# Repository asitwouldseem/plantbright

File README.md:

# plantbright
Just another A6211 based LED driver project for illuminating house plants.

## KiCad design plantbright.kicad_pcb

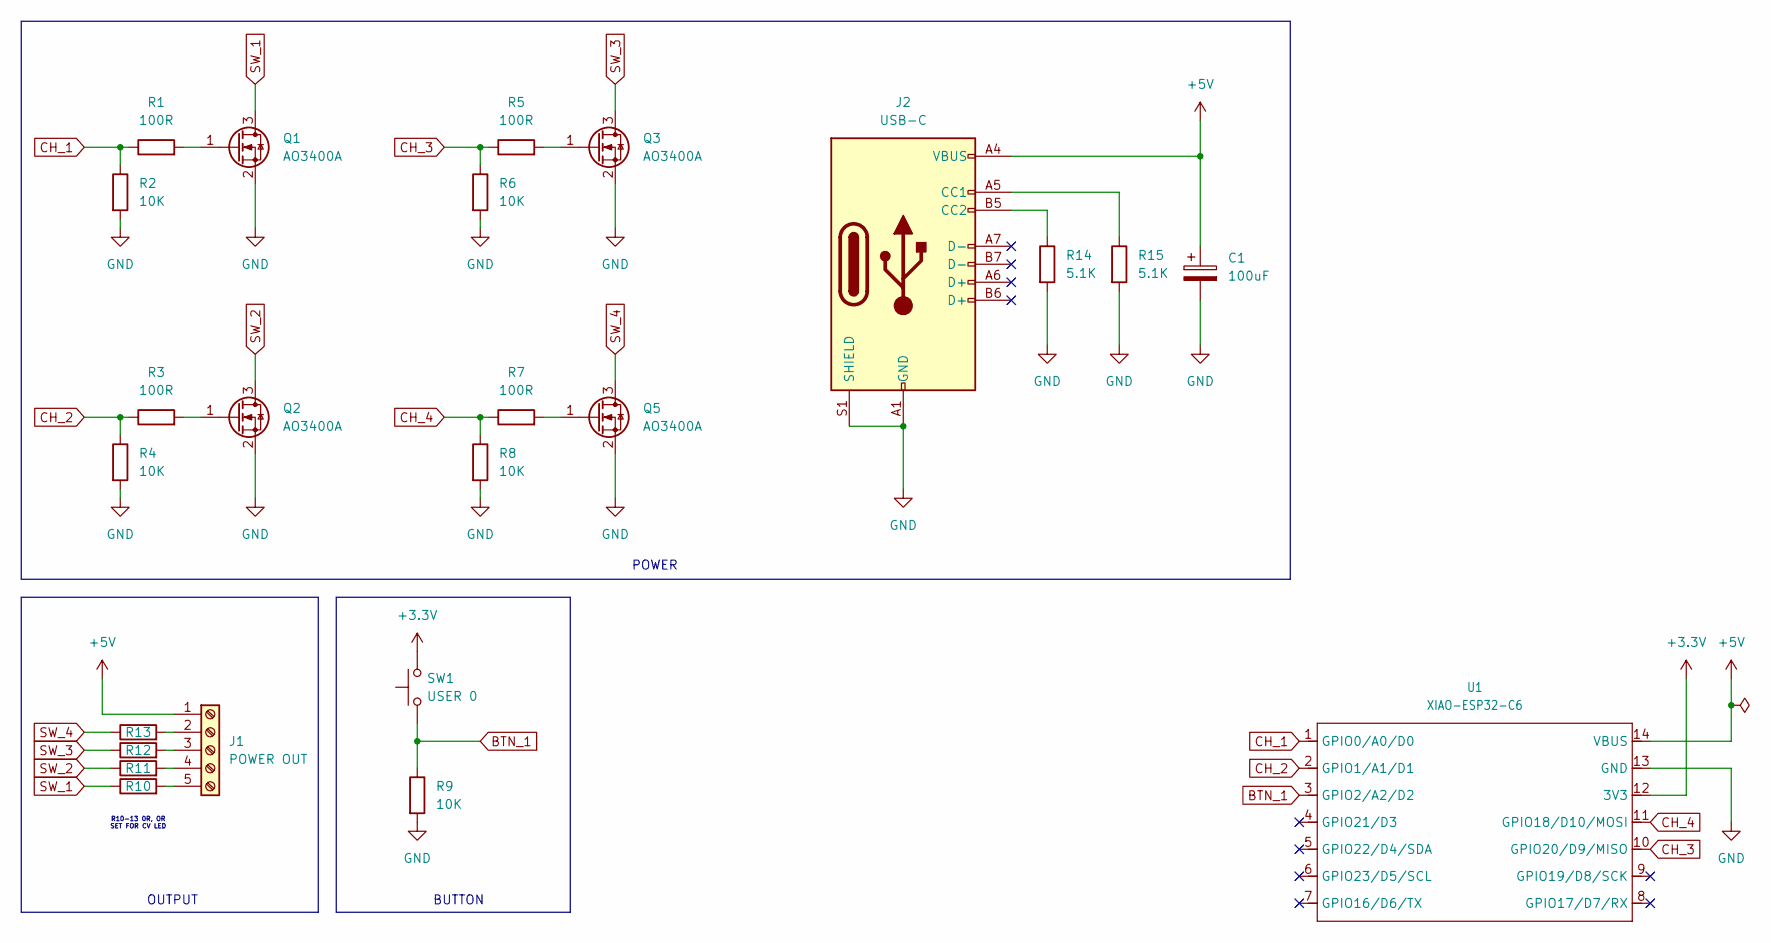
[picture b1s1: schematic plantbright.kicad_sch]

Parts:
C1: 100uF; C_1206_3216Metric_Pad1.33x1.80mm_HandSolder
J1: POWER OUT; TerminalBlock_Phoenix_MPT-0,5-5-2.54_1x05_P2.54mm_Horizontal
J2: USB-C; USB_C_Receptacle_HRO_TYPE-C-31-M-12
Q1, Q2, Q3, Q5: AO3400A; SOT-23
R1, R3, R5, R7: 100R; R_0805_2012Metric_Pad1.20x1.40mm_HandSolder
R2, R4, R6, R8, R9: 10K; R_0805_2012Metric_Pad1.20x1.40mm_HandSolder
R10, R11, R12, R13: 0R; R_1206_3216Metric_Pad1.30x1.75mm_HandSolder
R14, R15: 5.1K; R_0805_2012Metric_Pad1.20x1.40mm_HandSolder
SW1: USER 0; SW_PUSH_6mm
U1: XIAO-ESP32-C6; MOUDLE14P-XIAO-DIP-SMD

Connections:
+3.3V: SW1.2, U1.12 (3V3)
+5V: C1.1, J1.1, J2.A4 (VBUS), J2.A9 (VBUS), J2.B4 (VBUS), J2.B9 (VBUS), U1.14 (VBUS)
BTN_1: R9.1, SW1.1, U1.3 (GPIO2/A2/D2)
CH_1: R1.1, R2.1, U1.1 (GPIO0/A0/D0)
CH_2: R3.1, R4.1, U1.2 (GPIO1/A1/D1)
CH_3: R5.1, R6.1, U1.10 (GPIO20/D9/MISO)
CH_4: R7.1, R8.1, U1.11 (GPIO18/D10/MOSI)
GND: C1.2, J2.A1 (GND), J2.A12 (GND), J2.B1 (GND), J2.B12 (GND), J2.S1 (SHIELD), Q1.2 (S), Q2.2 (S), Q3.2 (S), Q5.2 (S), R2.2, R4.2, R6.2, R8.2, R9.2, R14.2, R15.2, U1.13 (GND)
unnamed: J1.2, R13.2
unnamed: J1.3, R12.2
unnamed: J1.4, R11.2
unnamed: J1.5, R10.2
unnamed: J2.A5 (CC1), R15.1
unnamed: J2.B5 (CC2), R14.1
unnamed: Q1.1 (G), R1.2
unnamed: Q2.1 (G), R3.2
unnamed: Q3.1 (G), R5.2
unnamed: Q5.1 (G), R7.2
SW_1: Q1.3 (D), R10.1
SW_2: Q2.3 (D), R11.1
SW_3: Q3.3 (D), R12.1
SW_4: Q5.3 (D), R13.1

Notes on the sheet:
POWER
BUTTON
R10-13 0R, OR SET FOR CV LED
OUTPUT

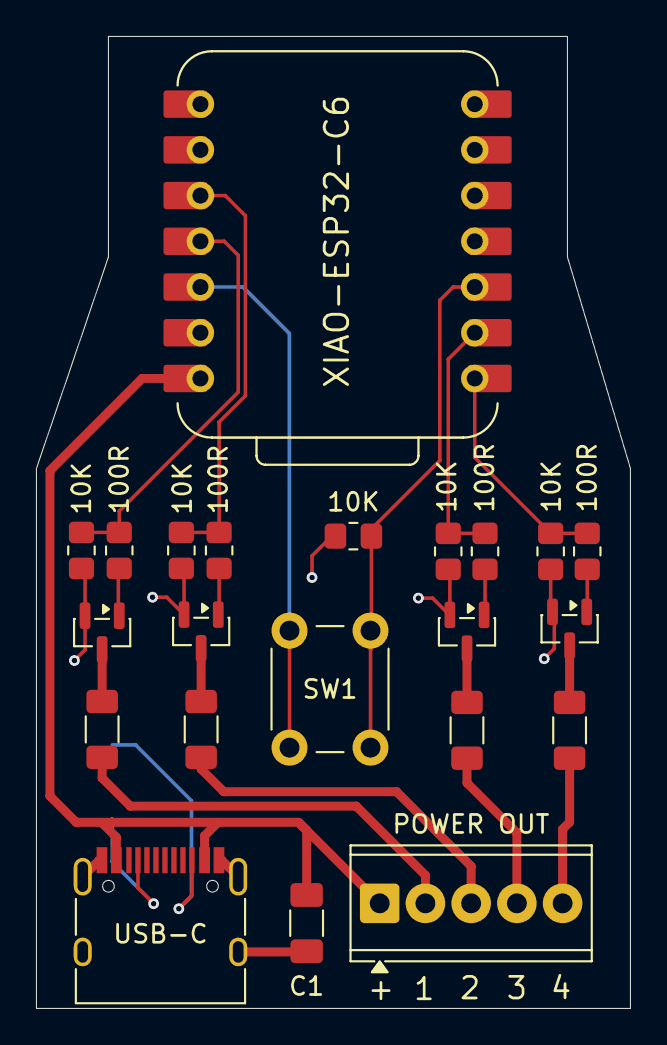
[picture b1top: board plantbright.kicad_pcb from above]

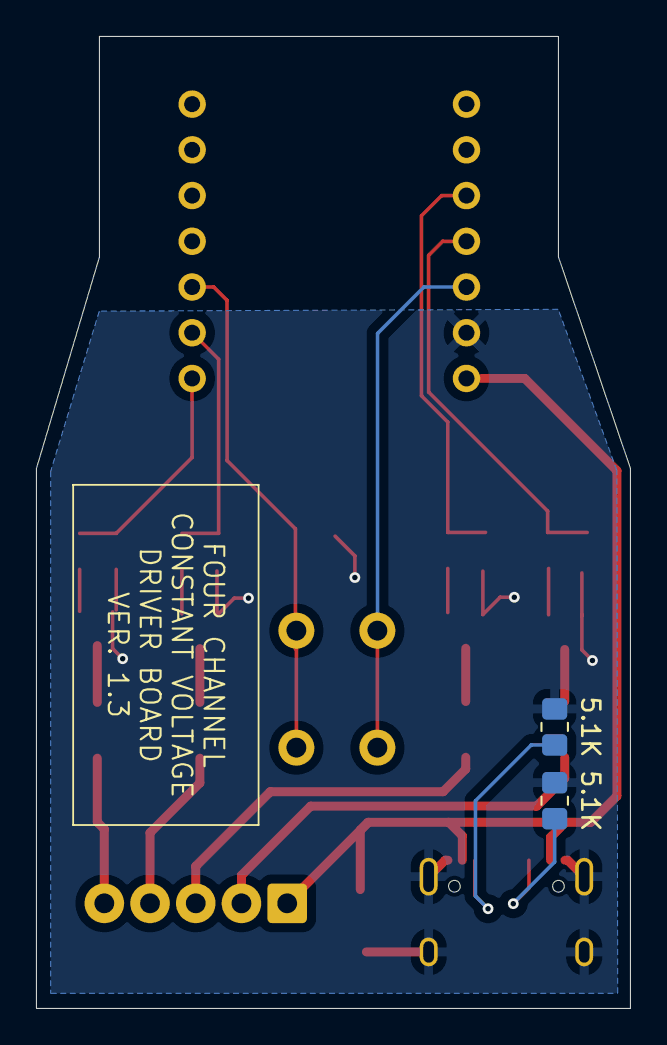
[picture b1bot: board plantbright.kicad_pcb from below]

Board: 2 copper layers, 33.0 x 54.0 mm, 24 parts (2 on the bottom side), 22 nets.

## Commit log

2026-02-23 init KiCad project
2026-02-23 Add temp MOSFET
2026-02-27 Wow, wow. Why a DF Player Mini?
2026-02-27 Start board layout
2026-02-27 Enough for now. Arranging bits.
2026-02-28 Add in dfplayermini board.
2026-02-28 Update `dfmini` library
2026-02-28 Start layout again
2026-02-28 Layout
2026-02-28 Add C6 text to silkscreen
2026-02-28 Enough for today.
2026-03-01 Remove dfplayer.
2026-03-01 Add current limiting resistors
2026-03-01 Happy with layout, yay!
2026-03-01 Pause. May be going CC.
2026-03-01 Yay. Back to CV.
2026-03-01 Layout 'ings
2026-03-01 Back to metric units.
2026-03-01 Enough for tonight, I think the shape works.
2026-03-01 Switch to screw terminals
2026-03-01 Ground pour
2026-03-02 Switch to USB-C
2026-03-02 Tidy pulldown resistor
2026-03-02 Tinkering
2026-03-02 Add cap
2026-03-02 DRC, getting there.
2026-03-02 Yay, V1.
2026-03-02 Move vias away from silkscreen
2026-03-02 Fix fills
2026-03-04 Tidy footprints for DRC, build prod.
2026-03-04 Add board label
2026-03-04 DFM fixes
